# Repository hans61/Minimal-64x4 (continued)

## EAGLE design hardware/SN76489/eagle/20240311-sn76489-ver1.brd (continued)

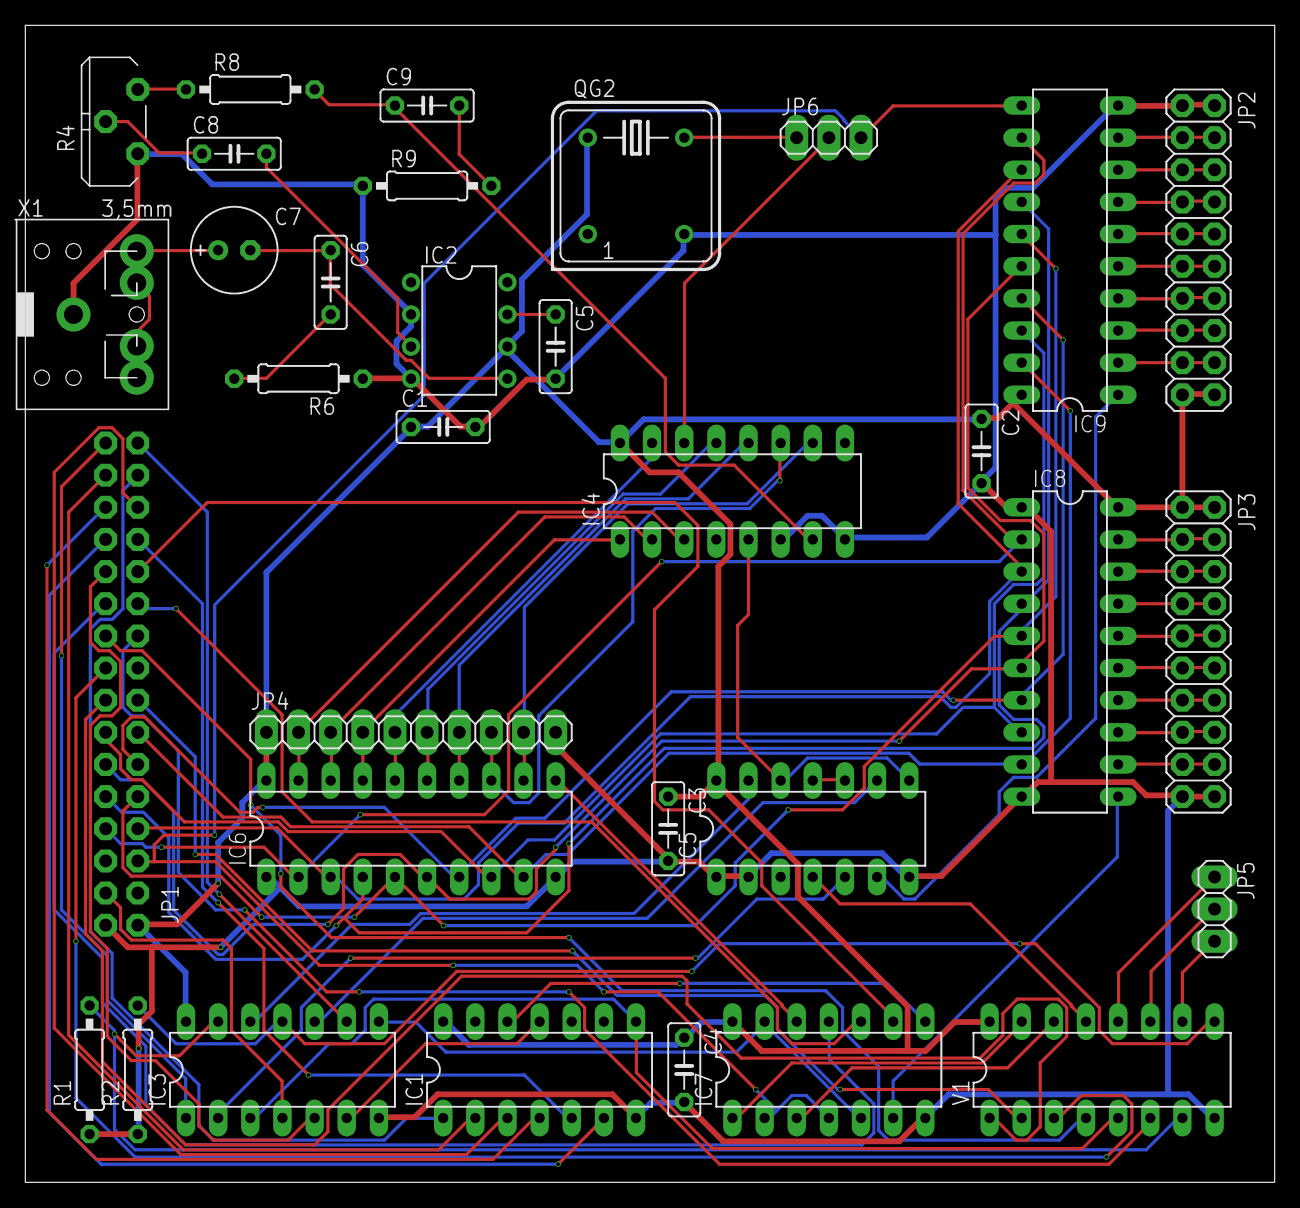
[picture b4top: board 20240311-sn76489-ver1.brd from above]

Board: 2 copper layers, 98.7 x 91.4 mm, 33 parts (1 on the bottom side), 84 nets.

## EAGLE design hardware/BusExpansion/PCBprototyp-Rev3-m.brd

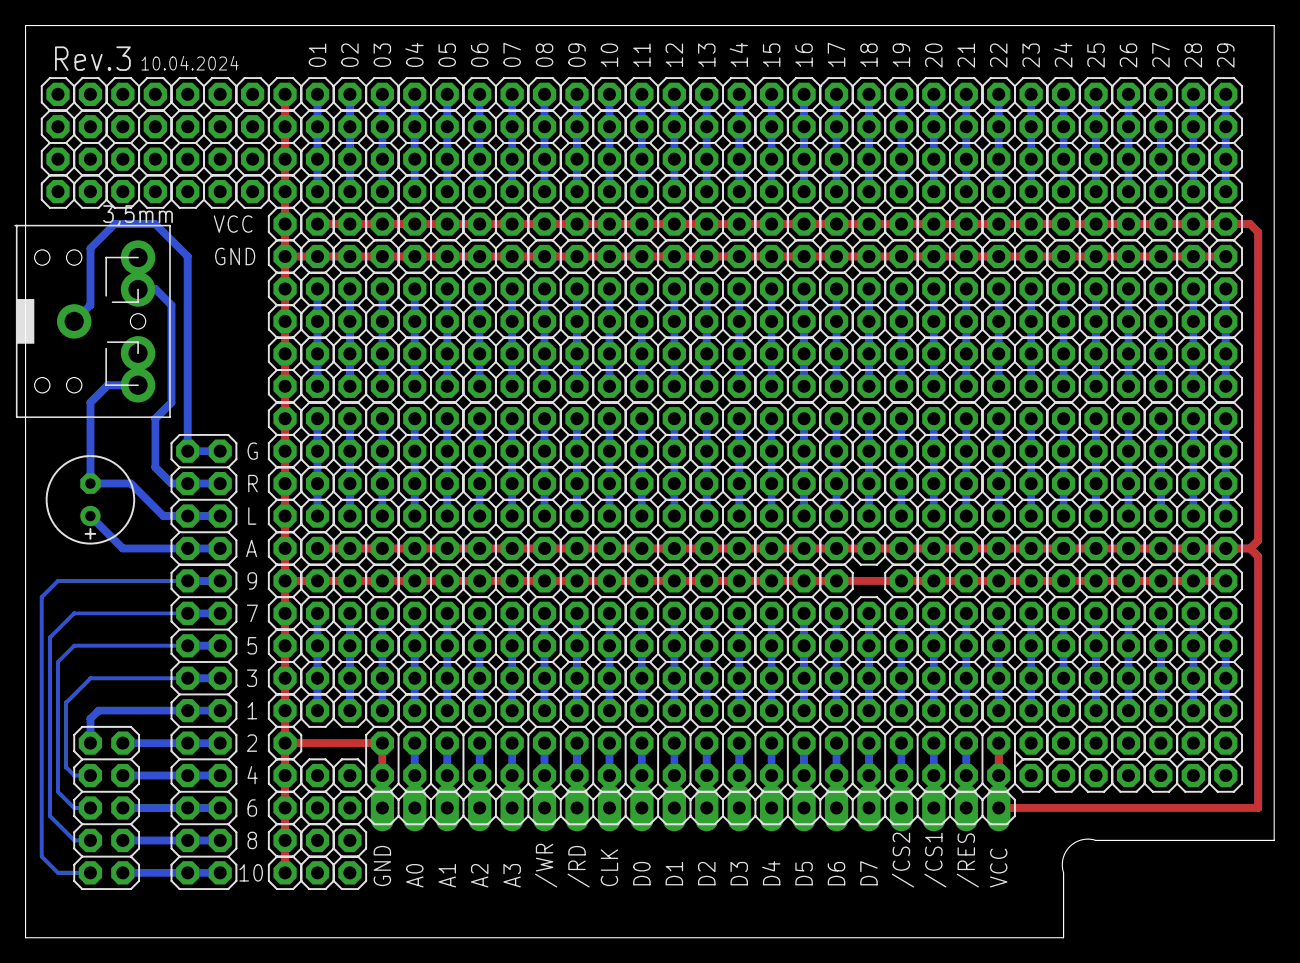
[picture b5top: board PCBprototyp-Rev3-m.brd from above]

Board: 2 copper layers, 97.8 x 71.4 mm, 661 parts (0 on the bottom side), 150 nets.

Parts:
C7: 220µF; E2,5-7
JP1: 1X20
JP2, JP5, JP6, JP7, JP8, JP9, JP10, JP11, JP12, JP13, JP14, JP15, JP16, JP17, JP18, JP19, JP20, JP21, JP22, JP23, JP24, JP26, JP27, JP28, JP29, JP30, JP31, JP32, JP33, JP34, JP35, JP36, JP37, JP38, JP39, JP40, JP41, JP42, JP43, JP44, JP45, JP46, JP47, JP48, JP49, JP50, JP51, JP52, JP53, JP54, JP55, JP56, JP57, JP58, JP59, JP60, JP61, JP62, JP63, JP64, JP65, JP66, JP67, JP68, JP69, JP70, JP71, JP72, JP73, JP74, JP75, JP76, JP77, JP78, JP79, JP80, JP81, JP82, JP83, JP84, JP85, JP86, JP87, JP88, JP89, JP90, JP91, JP92, JP93, JP96, JP97, JP98, JP99, JP100, JP101, JP102, JP103, JP104, JP105, JP106, JP107, JP108, JP109, JP110, JP111, JP112, JP113, JP114, JP115, JP116, JP117, JP118, JP119, JP120, JP121, JP122, JP123, JP124, JP125, JP126, JP127, JP128, JP129, JP130, JP131, JP132, JP133, JP134, JP135, JP136, JP137, JP138, JP139, JP140, JP141, JP142, JP143, JP144, JP145, JP146, JP147, JP148, JP149, JP150, JP151, JP152, JP153, JP154, JP155, JP156, JP157, JP158, JP159, JP160, JP161, JP162, JP163, JP164, JP165, JP166, JP167, JP168, JP169, JP170, JP171, JP172, JP173, JP174, JP175, JP176, JP177, JP178, JP179, JP180, JP181, JP182, JP183, JP184, JP185, JP186, JP187, JP188, JP189, JP190, JP191, JP192, JP193, JP194, JP195, JP196, JP197, JP198, JP199, JP200, JP201, JP202, JP203, JP204, JP205, JP206, JP207, JP208, JP209, JP210, JP211, JP212, JP213, JP214, JP215, JP216, JP217, JP218, JP219, JP220, JP221, JP222, JP223, JP224, JP225, JP226, JP227, JP228, JP229, JP230, JP231, JP232, JP233, JP234, JP235, JP236, JP237, JP238, JP239, JP240, JP241, JP242, JP243, JP244, JP245, JP246, JP247, JP248, JP249, JP250, JP251, JP252, JP253, JP254, JP255, JP256, JP257, JP258, JP259, JP260, JP261, JP262, JP263, JP264, JP265, JP266, JP267, JP268, JP269, JP270, JP271, JP272, JP273, JP274, JP275, JP276, JP277, JP278, JP279, JP280, JP281, JP282, JP283, JP284, JP285, JP286, JP287, JP288, JP289, JP290, JP291, JP292, JP293, JP294, JP295, JP296, JP297, JP298, JP299, JP300, JP301, JP302, JP303, JP304, JP305, JP306, JP307, JP308, JP309, JP310, JP311, JP312, JP313, JP314, JP315, JP316, JP317, JP318, JP319, JP320, JP321, JP322, JP323, JP324, JP325, JP326, JP327, JP328, JP329, JP330, JP331, JP332, JP333, JP334, JP335, JP336, JP337, JP338, JP339, JP340, JP341, JP342, JP343, JP344, JP345, JP346, JP347, JP348, JP349, JP350, JP351, JP352, JP353, JP354, JP355, JP356, JP357, JP358, JP359, JP360, JP361, JP362, JP363, JP364, JP365, JP366, JP367, JP368, JP369, JP370, JP371, JP372, JP373, JP374, JP375, JP376, JP377, JP378, JP379, JP380, JP381, JP382, JP383, JP384, JP385, JP386, JP387, JP388, JP389, JP390, JP391, JP392, JP393, JP394, JP395, JP396, JP397, JP398, JP399, JP400, JP401, JP402, JP403, JP404, JP405, JP406, JP407, JP408, JP409, JP410, JP411, JP412, JP413, JP414, JP415, JP416, JP417, JP418, JP419, JP420, JP421, JP422, JP423, JP424, JP425, JP426, JP427, JP428, JP429, JP430, JP431, JP432, JP433, JP434, JP435, JP436, JP437, JP438, JP439, JP440, JP441, JP442, JP443, JP444, JP445, JP446, JP447, JP448, JP449, JP450, JP451, JP452, JP453, JP454, JP455, JP456, JP457, JP458, JP459, JP460, JP461, JP462, JP463, JP464, JP465, JP466, JP467, JP468, JP469, JP470, JP471, JP472, JP473, JP474, JP475, JP476, JP477, JP478, JP479, JP480, JP481, JP482, JP483, JP484, JP485, JP486, JP487, JP488, JP489, JP490, JP491, JP492, JP493, JP494, JP495, JP496, JP497, JP498, JP499, JP500, JP501, JP502, JP503, JP504, JP505, JP506, JP507, JP508, JP509, JP510, JP511, JP512, JP513, JP514, JP515, JP516, JP517, JP518, JP519, JP520, JP521, JP522, JP523, JP524, JP525, JP526, JP527, JP528, JP529, JP530, JP531, JP532, JP533, JP534, JP535, JP536, JP537, JP538, JP539, JP540, JP541, JP542, JP543, JP544, JP545, JP546, JP547, JP548, JP549, JP550, JP551, JP552, JP553, JP554, JP555, JP556, JP557, JP558, JP559, JP560, JP561, JP562, JP563, JP564, JP565, JP566, JP567, JP568, JP569, JP570, JP571, JP572, JP573, JP574, JP575, JP576, JP577, JP578, JP579, JP580, JP581, JP582, JP583, JP584, JP585, JP586, JP587, JP588, JP589, JP590, JP591, JP592, JP593, JP594, JP595, JP596, JP597, JP598, JP599, JP600, JP601, JP602, JP603, JP604, JP605, JP606, JP607, JP608, JP609, JP610, JP611, JP612, JP613, JP614, JP615, JP616, JP617, JP618, JP619, JP620, JP621, JP622, JP623, JP624, JP625, JP626, JP627, JP628, JP629, JP630, JP631, JP632, JP633, JP634, JP635, JP636, JP637, JP638, JP639, JP640, JP641, JP642, JP643, JP644, JP645, JP646, JP647, JP648, JP649, JP650, JP651, JP652, JP653, JP654, JP655, JP656, JP657, JP658, JP659, JP660: 1X01
JP3: 2X20
JP4: 2X10
JP94: 2X05
JP95: 2X04
X1: AUX1; SJ1-352XN

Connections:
/CS2: JP1.4, JP3.7, JP3.8
/RD: JP1.14, JP3.27, JP3.28
/RES: JP1.2, JP3.3, JP3.4
/WR: JP1.15, JP3.29, JP3.30
A0: JP1.19, JP3.37, JP3.38
A1: JP1.18, JP3.35, JP3.36
A2: JP1.17, JP3.33, JP3.34
A3: JP1.16, JP3.31, JP3.32
CLK: JP1.13, JP3.25, JP3.26
CS1: JP1.3, JP3.5, JP3.6
D0: JP1.12, JP3.23, JP3.24
D1: JP1.11, JP3.21, JP3.22
D2: JP1.10, JP3.19, JP3.20
D3: JP1.9, JP3.17, JP3.18
D4: JP1.8, JP3.15, JP3.16
D5: JP1.7, JP3.13, JP3.14
D6: JP1.6, JP3.11, JP3.12
D7: JP1.5, JP3.9, JP3.10
GND: JP1.20, JP2.1, JP3.39, JP3.40, JP9.1, JP10.1, JP11.1, JP12.1, JP13.1, JP14.1, JP15.1, JP16.1, JP17.1, JP18.1, JP19.1, JP20.1, JP21.1, JP22.1, JP23.1, JP24.1, JP26.1, JP27.1, JP28.1, JP29.1, JP30.1, JP31.1, JP32.1, JP33.1, JP69.1, JP70.1, JP71.1, JP72.1, JP73.1, JP74.1, JP75.1, JP76.1, JP77.1, JP78.1, JP79.1, JP80.1, JP81.1, JP82.1, JP83.1, JP84.1, JP85.1, JP86.1, JP87.1, JP88.1, JP89.1, JP90.1, JP91.1, JP92.1, JP93.1, JP96.1, JP97.1, JP98.1, JP140.1, JP141.1, JP142.1, JP143.1, JP144.1, JP145.1, JP146.1, JP147.1, JP148.1, JP149.1, JP150.1, JP151.1, JP152.1, JP153.1, JP154.1, JP155.1, JP156.1, JP157.1, JP158.1, JP159.1, JP160.1, JP161.1, JP162.1, JP163.1, JP164.1, JP165.1, JP166.1, JP167.1, JP168.1
unnamed: C7.-, JP95.3, JP95.4, X1.2, X1.10
unnamed: JP95.5, JP95.6, X1.3, X1.11
unnamed: JP95.7, JP95.8, X1.1
unnamed: C7.+, JP95.1, JP95.2
unnamed: JP103.1, JP104.1, JP105.1, JP106.1
unnamed: JP4.17, JP4.18, JP94.7
unnamed: JP4.15, JP4.16, JP94.5
unnamed: JP4.13, JP4.14, JP94.3
unnamed: JP4.11, JP4.12, JP94.1
unnamed: JP4.9, JP4.10, JP94.2
unnamed: JP4.7, JP4.8, JP94.4
unnamed: JP4.5, JP4.6, JP94.6
unnamed: JP4.3, JP4.4, JP94.8
unnamed: JP5.1, JP6.1, JP7.1, JP8.1
unnamed: JP59.1, JP60.1, JP61.1, JP62.1
unnamed: JP4.1, JP4.2, JP94.10
unnamed: JP4.19, JP4.20, JP94.9
unnamed: JP107.1, JP108.1, JP109.1, JP110.1
unnamed: JP63.1, JP64.1, JP65.1, JP66.1
unnamed: JP67.1, JP68.1, JP169.1, JP170.1
unnamed: JP178.1, JP179.1, JP180.1, JP181.1
unnamed: JP182.1, JP183.1, JP184.1, JP185.1
unnamed: JP186.1, JP187.1, JP188.1, JP189.1
unnamed: JP190.1, JP191.1, JP192.1, JP193.1
unnamed: JP194.1, JP195.1, JP196.1, JP197.1
unnamed: JP198.1, JP199.1, JP200.1, JP201.1
unnamed: JP202.1, JP203.1, JP204.1, JP205.1
unnamed: JP206.1, JP207.1, JP208.1, JP209.1
unnamed: JP210.1, JP211.1, JP212.1, JP213.1
unnamed: JP214.1, JP215.1, JP216.1, JP217.1
unnamed: JP218.1, JP219.1, JP220.1, JP221.1
unnamed: JP222.1, JP223.1, JP224.1, JP225.1
unnamed: JP226.1, JP227.1, JP228.1, JP229.1
unnamed: JP230.1, JP231.1, JP232.1, JP233.1
unnamed: JP234.1, JP235.1, JP236.1, JP237.1
unnamed: JP238.1, JP239.1, JP240.1, JP241.1
unnamed: JP242.1, JP243.1, JP244.1, JP245.1
unnamed: JP246.1, JP247.1, JP248.1, JP249.1
unnamed: JP250.1, JP251.1, JP252.1, JP253.1
unnamed: JP254.1, JP255.1, JP256.1, JP257.1
unnamed: JP258.1, JP259.1, JP260.1, JP261.1
unnamed: JP262.1, JP263.1, JP264.1, JP265.1
unnamed: JP266.1, JP267.1, JP268.1, JP269.1
unnamed: JP270.1, JP271.1, JP272.1, JP273.1
unnamed: JP274.1, JP275.1, JP276.1, JP277.1
unnamed: JP278.1, JP279.1, JP280.1, JP281.1
unnamed: JP282.1, JP283.1, JP284.1, JP285.1
unnamed: JP286.1, JP287.1, JP288.1, JP289.1
unnamed: JP290.1, JP291.1, JP292.1, JP293.1
unnamed: JP294.1, JP295.1, JP296.1, JP297.1
unnamed: JP298.1, JP299.1, JP300.1, JP301.1
unnamed: JP302.1, JP303.1, JP304.1, JP305.1
unnamed: JP306.1, JP307.1, JP308.1, JP309.1
unnamed: JP310.1, JP311.1, JP312.1, JP313.1
unnamed: JP314.1, JP315.1, JP316.1, JP317.1
unnamed: JP318.1, JP319.1, JP320.1, JP321.1
unnamed: JP322.1, JP323.1, JP324.1, JP325.1
unnamed: JP326.1, JP327.1, JP328.1, JP329.1
unnamed: JP330.1, JP331.1, JP332.1, JP333.1
unnamed: JP334.1, JP335.1, JP336.1, JP337.1
unnamed: JP338.1, JP339.1, JP340.1, JP341.1
unnamed: JP342.1, JP343.1, JP344.1, JP345.1
unnamed: JP346.1, JP347.1, JP348.1, JP349.1
unnamed: JP350.1, JP351.1, JP352.1, JP353.1
unnamed: JP354.1, JP355.1, JP356.1, JP357.1
unnamed: JP358.1, JP359.1, JP360.1, JP361.1
unnamed: JP362.1, JP363.1, JP364.1, JP365.1
unnamed: JP366.1, JP367.1, JP368.1, JP369.1
unnamed: JP370.1, JP371.1, JP372.1, JP373.1
unnamed: JP374.1, JP375.1, JP376.1, JP377.1
unnamed: JP378.1, JP379.1, JP380.1, JP381.1
unnamed: JP382.1, JP383.1, JP384.1, JP385.1
unnamed: JP386.1, JP387.1, JP388.1, JP389.1
unnamed: JP390.1, JP391.1, JP392.1, JP393.1
unnamed: JP394.1, JP395.1, JP396.1, JP397.1
unnamed: JP398.1, JP399.1, JP400.1, JP401.1
unnamed: JP402.1, JP403.1, JP404.1, JP405.1
unnamed: JP406.1, JP407.1, JP408.1, JP409.1
unnamed: JP410.1, JP411.1, JP412.1, JP413.1
unnamed: JP414.1, JP415.1, JP416.1, JP417.1
unnamed: JP418.1, JP419.1, JP420.1, JP421.1
unnamed: JP422.1, JP423.1, JP424.1, JP425.1
unnamed: JP426.1, JP427.1, JP428.1, JP429.1
unnamed: JP430.1, JP431.1, JP432.1, JP433.1
unnamed: JP434.1, JP435.1, JP436.1, JP437.1
unnamed: JP438.1, JP439.1, JP440.1, JP441.1
unnamed: JP442.1, JP443.1, JP444.1, JP445.1
unnamed: JP446.1, JP447.1, JP448.1, JP449.1
unnamed: JP450.1, JP451.1, JP452.1, JP453.1
unnamed: JP454.1, JP455.1, JP456.1, JP457.1
unnamed: JP458.1, JP459.1, JP460.1, JP461.1
unnamed: JP462.1, JP463.1, JP464.1, JP465.1
unnamed: JP466.1, JP467.1, JP468.1, JP469.1
unnamed: JP470.1, JP471.1, JP472.1, JP473.1
unnamed: JP474.1, JP475.1, JP476.1, JP477.1
unnamed: JP478.1, JP479.1, JP480.1, JP481.1
unnamed: JP482.1, JP483.1, JP484.1, JP485.1
unnamed: JP486.1, JP487.1, JP488.1, JP489.1
unnamed: JP490.1, JP491.1, JP492.1, JP493.1
unnamed: JP494.1, JP495.1, JP496.1, JP497.1
unnamed: JP498.1, JP499.1, JP500.1, JP501.1
unnamed: JP502.1, JP503.1, JP504.1, JP505.1
unnamed: JP549.1, JP550.1, JP551.1, JP552.1
unnamed: JP553.1, JP554.1, JP555.1, JP556.1
unnamed: JP557.1, JP558.1, JP559.1, JP560.1
unnamed: JP561.1, JP562.1, JP563.1, JP564.1
unnamed: JP565.1, JP566.1, JP567.1, JP568.1
unnamed: JP569.1, JP570.1, JP571.1, JP572.1
unnamed: JP573.1, JP574.1, JP575.1, JP576.1
unnamed: JP577.1, JP578.1, JP579.1, JP580.1
unnamed: JP581.1, JP582.1, JP583.1, JP584.1
unnamed: JP585.1, JP586.1, JP587.1, JP588.1
unnamed: JP589.1, JP590.1, JP591.1, JP592.1
unnamed: JP593.1, JP594.1, JP595.1, JP596.1
unnamed: JP597.1, JP598.1, JP599.1, JP600.1
unnamed: JP601.1, JP602.1, JP603.1, JP604.1
unnamed: JP605.1, JP606.1, JP607.1, JP608.1
unnamed: JP609.1, JP610.1, JP611.1, JP612.1
unnamed: JP613.1, JP614.1, JP615.1, JP616.1
unnamed: JP617.1, JP618.1, JP619.1, JP620.1
unnamed: JP621.1, JP622.1, JP623.1, JP624.1
unnamed: JP625.1, JP626.1, JP627.1, JP628.1
unnamed: JP629.1, JP630.1, JP631.1, JP632.1
unnamed: JP633.1, JP634.1, JP635.1, JP636.1
unnamed: JP637.1, JP638.1, JP639.1, JP640.1
unnamed: JP641.1, JP642.1, JP643.1, JP644.1
unnamed: JP645.1, JP646.1, JP647.1, JP648.1
unnamed: JP649.1, JP650.1, JP651.1, JP652.1
unnamed: JP653.1, JP654.1, JP655.1, JP656.1
unnamed: JP657.1, JP658.1, JP659.1, JP660.1
VCC: JP1.1, JP3.1, JP3.2, JP34.1, JP35.1, JP36.1, JP37.1, JP38.1, JP39.1, JP40.1, JP41.1, JP42.1, JP43.1, JP44.1, JP45.1, JP46.1, JP47.1, JP48.1, JP49.1, JP50.1, JP51.1, JP52.1, JP53.1, JP54.1, JP55.1, JP56.1, JP57.1, JP58.1, JP99.1, JP100.1, JP101.1, JP102.1, JP111.1, JP112.1, JP113.1, JP114.1, JP115.1, JP116.1, JP117.1, JP118.1, JP119.1, JP120.1, JP121.1, JP122.1, JP123.1, JP124.1, JP125.1, JP126.1, JP127.1, JP128.1, JP129.1, JP130.1, JP131.1, JP132.1, JP133.1, JP134.1, JP135.1, JP136.1, JP137.1, JP138.1, JP139.1

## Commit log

2024-04-02 first things added
2024-04-02 readme changed
2024-04-02 readme changed, added mp3
2024-04-07 added test 82c55
2024-04-07 added picture to test 82c55
2024-04-07 changed picture test 82c55
2024-05-11 added first test board
2024-05-11 readme changed*
2024-05-12 added BusExpansion
2024-06-02 the next version of an extension
2024-06-02 sd card for minimal64x4
2024-06-02 read write sector
2024-06-16 new expansion with sd card
2024-06-18 vgm examples added
2024-06-22 Fixed an error when accessing data that requires more than one cluster.
2024-07-20 Improved optics labeling PCB
2024-07-20 play vgc from sd card
2025-03-08 restructuring
